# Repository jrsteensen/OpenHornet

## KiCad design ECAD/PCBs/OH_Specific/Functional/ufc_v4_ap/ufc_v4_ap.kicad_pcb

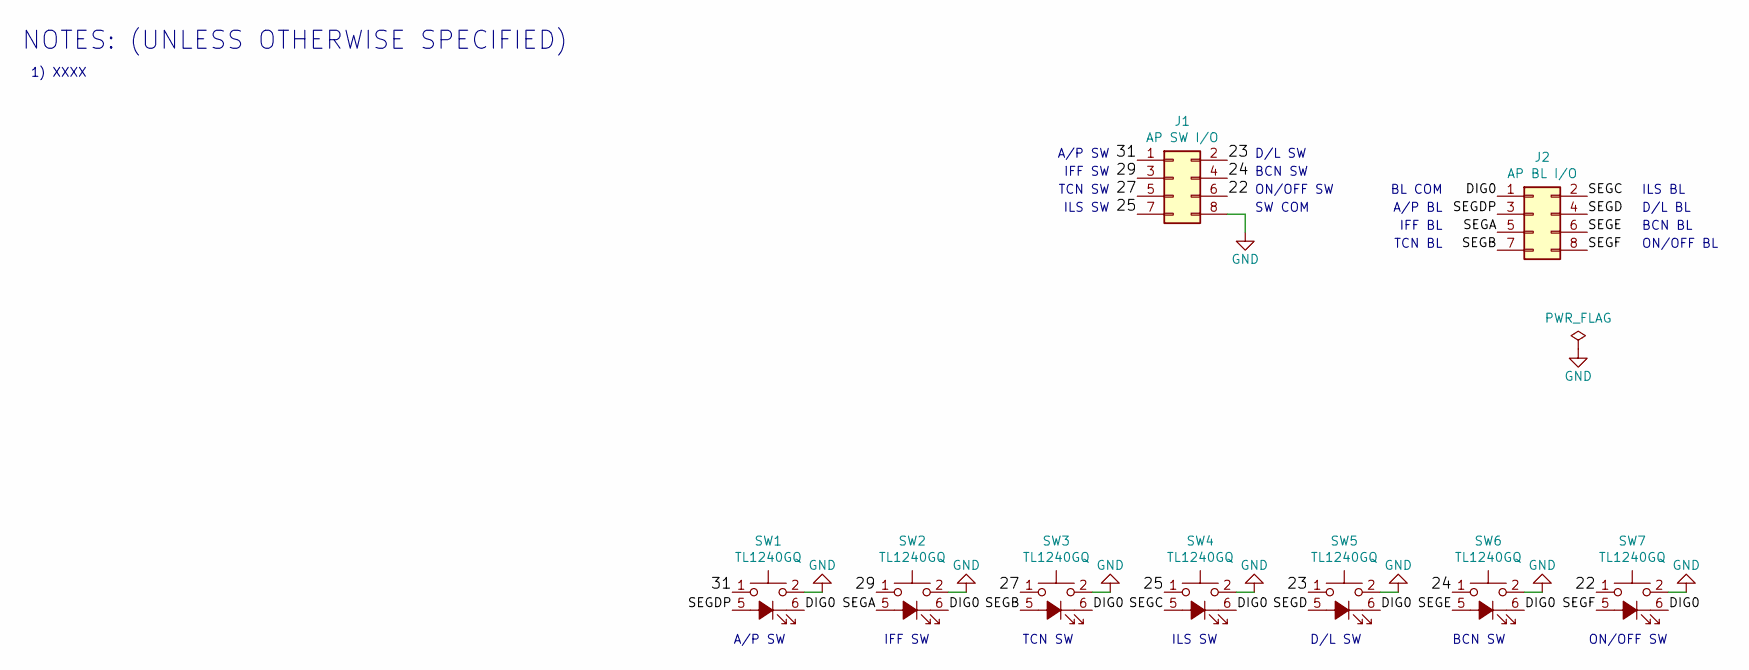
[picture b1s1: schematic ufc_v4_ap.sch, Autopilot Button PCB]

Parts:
J1: AP SW I/O; PinHeader_2x04_P2.54mm_Vertical
J2: AP BL I/O; PinHeader_2x04_P2.54mm_Vertical
SW1, SW2, SW3, SW4, SW5, SW6, SW7: TL1240GQ

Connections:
/22: J1.6, SW7.1
/23: J1.2, SW5.1
/24: J1.4, SW6.1
/25: J1.7, SW4.1
/27: J1.5, SW3.1
/29: J1.3, SW2.1
/31: J1.1, SW1.1
/DIG0: J2.1, SW1.6, SW2.6, SW3.6, SW4.6, SW5.6, SW6.6, SW7.6
/SEGA: J2.5, SW2.5 (K)
/SEGB: J2.7, SW3.5 (K)
/SEGC: J2.2, SW4.5 (K)
/SEGD: J2.4, SW5.5 (K)
/SEGDP: J2.3, SW1.5 (K)
/SEGE: J2.6, SW6.5 (K)
/SEGF: J2.8, SW7.5 (K)
GND: J1.8, SW1.2, SW2.2, SW3.2, SW4.2, SW5.2, SW6.2, SW7.2

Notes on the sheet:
NOTES: (UNLESS OTHERWISE SPECIFIED)
1) XXXX
A/P SW
IFF SW
TCN SW
ILS SW
D/L SW
BCN SW
ON/OFF SW
BL COM
A/P BL
IFF BL
TCN BL
ILS BL
D/L BL
BCN BL
ON/OFF BL
SW COM

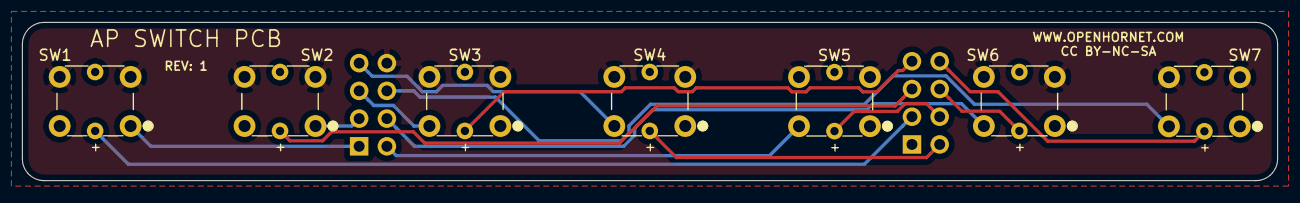
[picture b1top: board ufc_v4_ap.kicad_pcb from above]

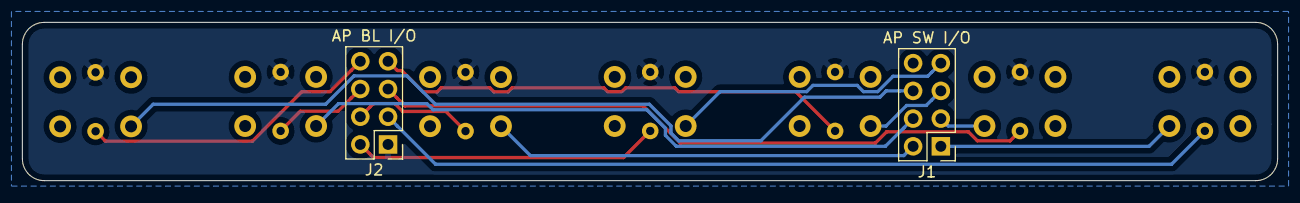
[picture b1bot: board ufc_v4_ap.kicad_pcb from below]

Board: 2 copper layers, 115.0 x 14.5 mm, 9 parts (2 on the bottom side), 16 nets.

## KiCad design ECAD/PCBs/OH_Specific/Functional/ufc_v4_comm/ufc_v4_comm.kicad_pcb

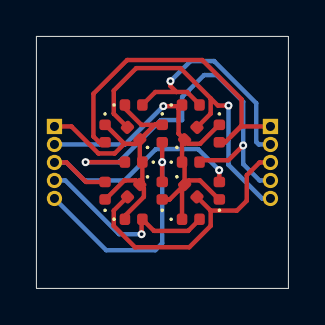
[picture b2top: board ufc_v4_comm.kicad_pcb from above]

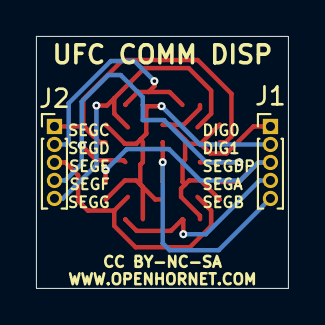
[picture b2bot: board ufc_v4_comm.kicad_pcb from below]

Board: 2 copper layers, 14.0 x 14.0 mm, 18 parts (2 on the bottom side), 10 nets.

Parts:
D1, D2, D3, D4, D5, D6, D7, D8, D9, D10, D11, D12, D13, D14, D15, D16: LED; LED_0402_1005Metric
J1, J2: Conn_01x05_Male; PinHeader_1x05_P1.00mm_Vertical

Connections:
/DIG0: D1.1, D2.1, D3.1, D4.1, D5.1, D6.1, D7.1, D8.1, J1.1
/DIG1: D9.1, D10.1, D11.1, D12.1, D13.1, D14.1, D15.1, D16.1, J1.2
/SEGA: D7.2, D14.2, J1.4
/SEGB: D8.2, D9.2, J1.5
/SEGC: D1.2, D15.2, J2.1
/SEGD: D3.2, D10.2, J2.2
/SEGDP: D2.2, D16.2, J1.3
/SEGE: D6.2, D13.2, J2.3
/SEGF: D5.2, D12.2, J2.4
/SEGG: D4.2, D11.2, J2.5

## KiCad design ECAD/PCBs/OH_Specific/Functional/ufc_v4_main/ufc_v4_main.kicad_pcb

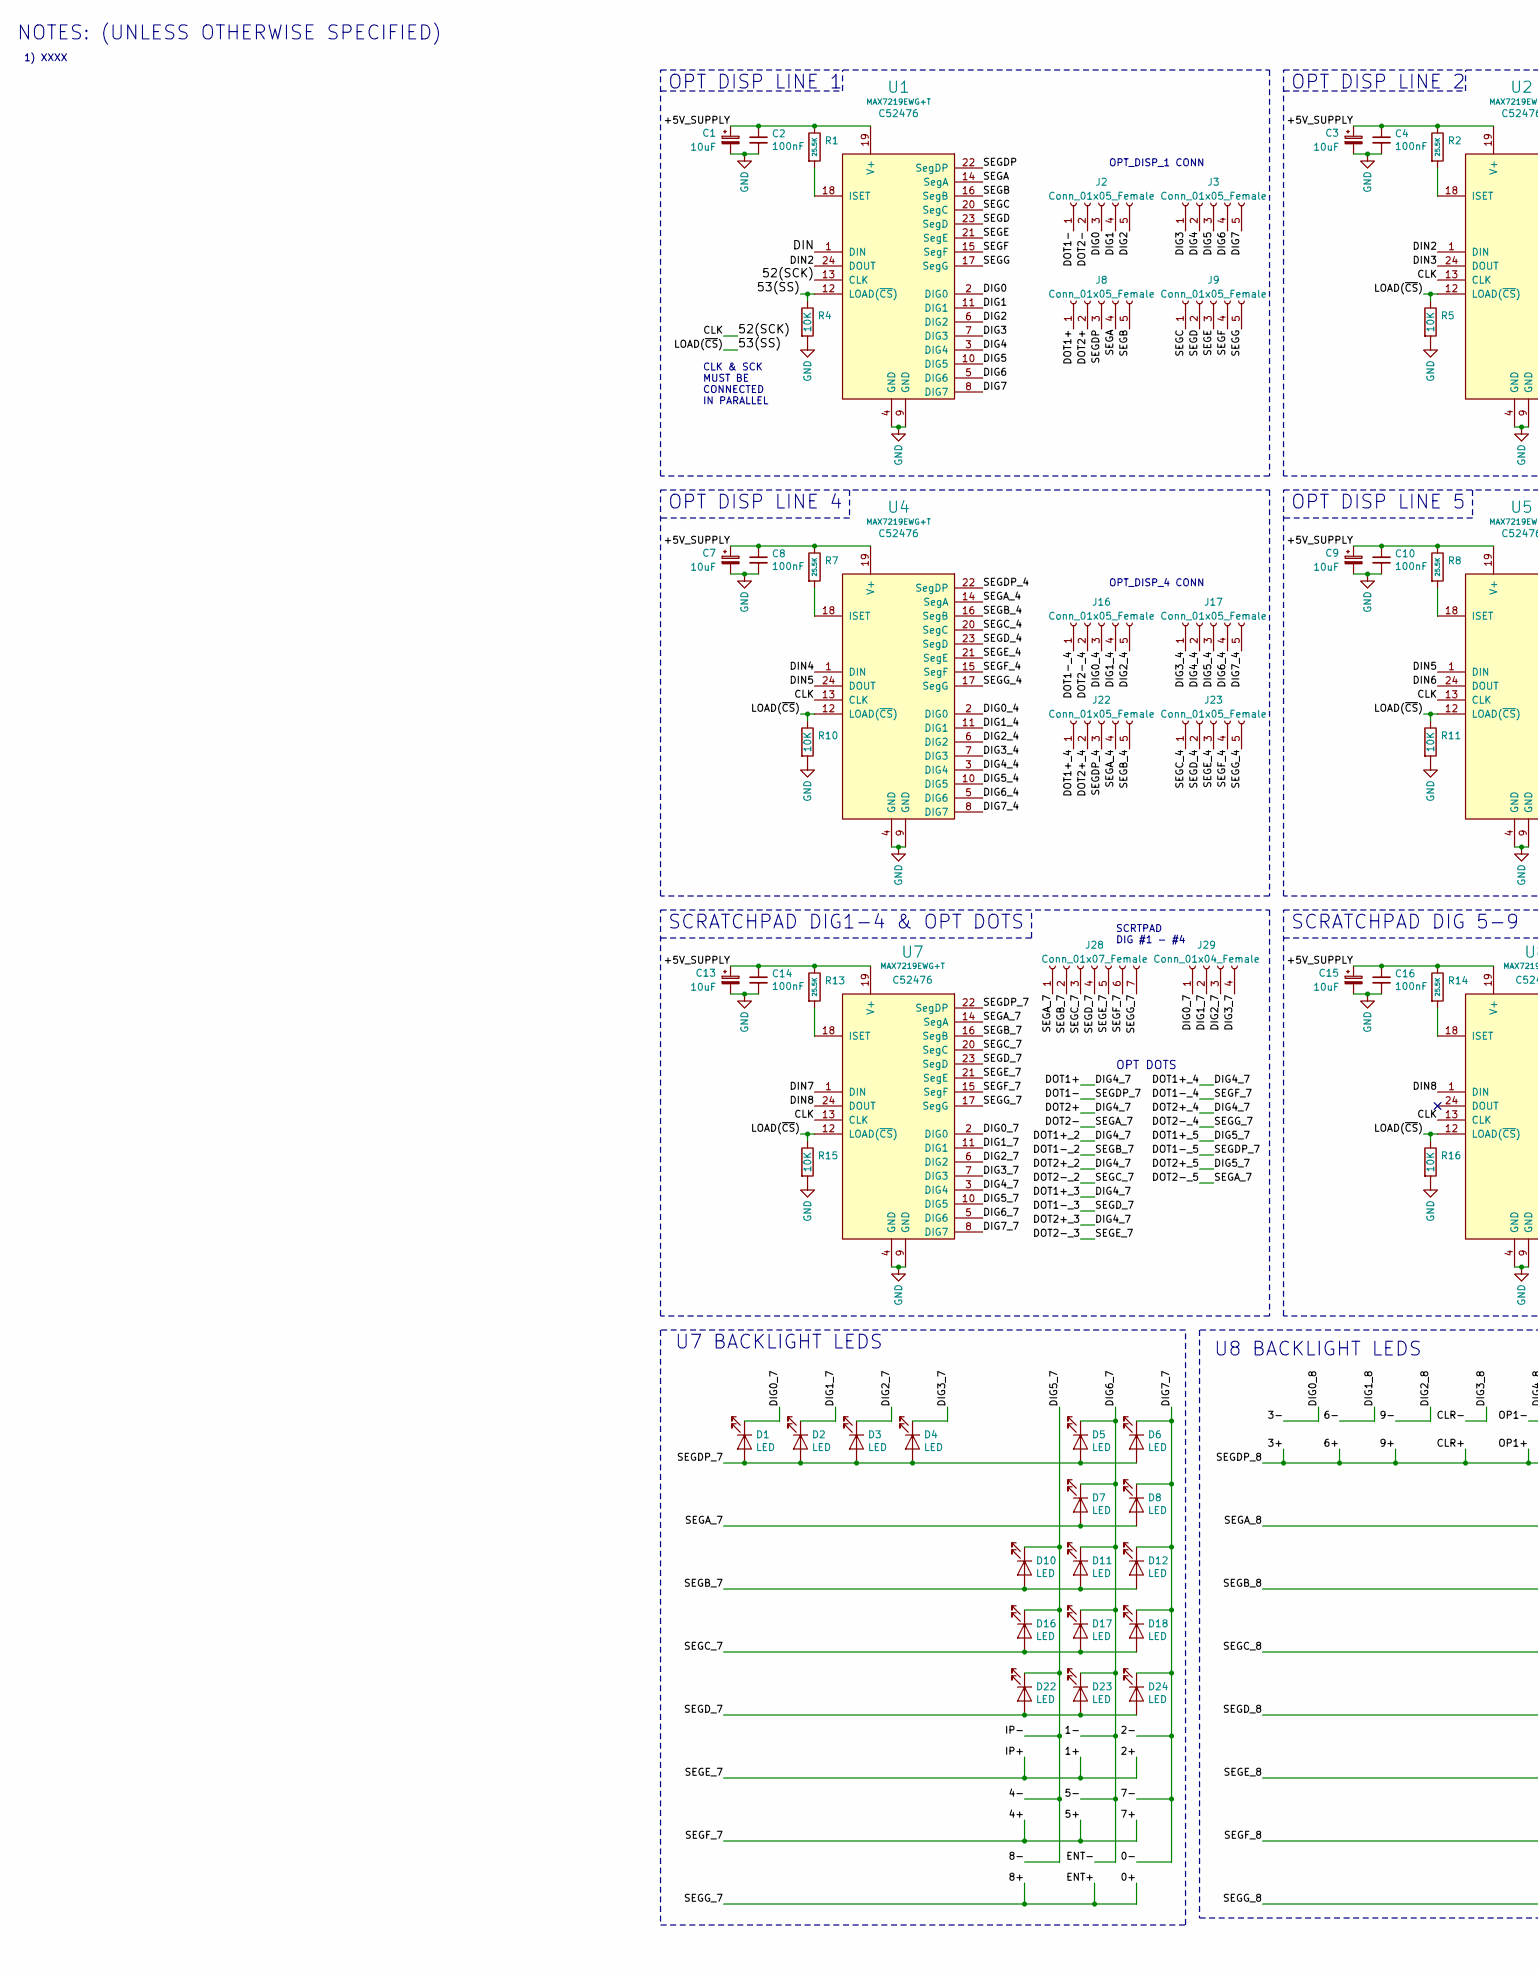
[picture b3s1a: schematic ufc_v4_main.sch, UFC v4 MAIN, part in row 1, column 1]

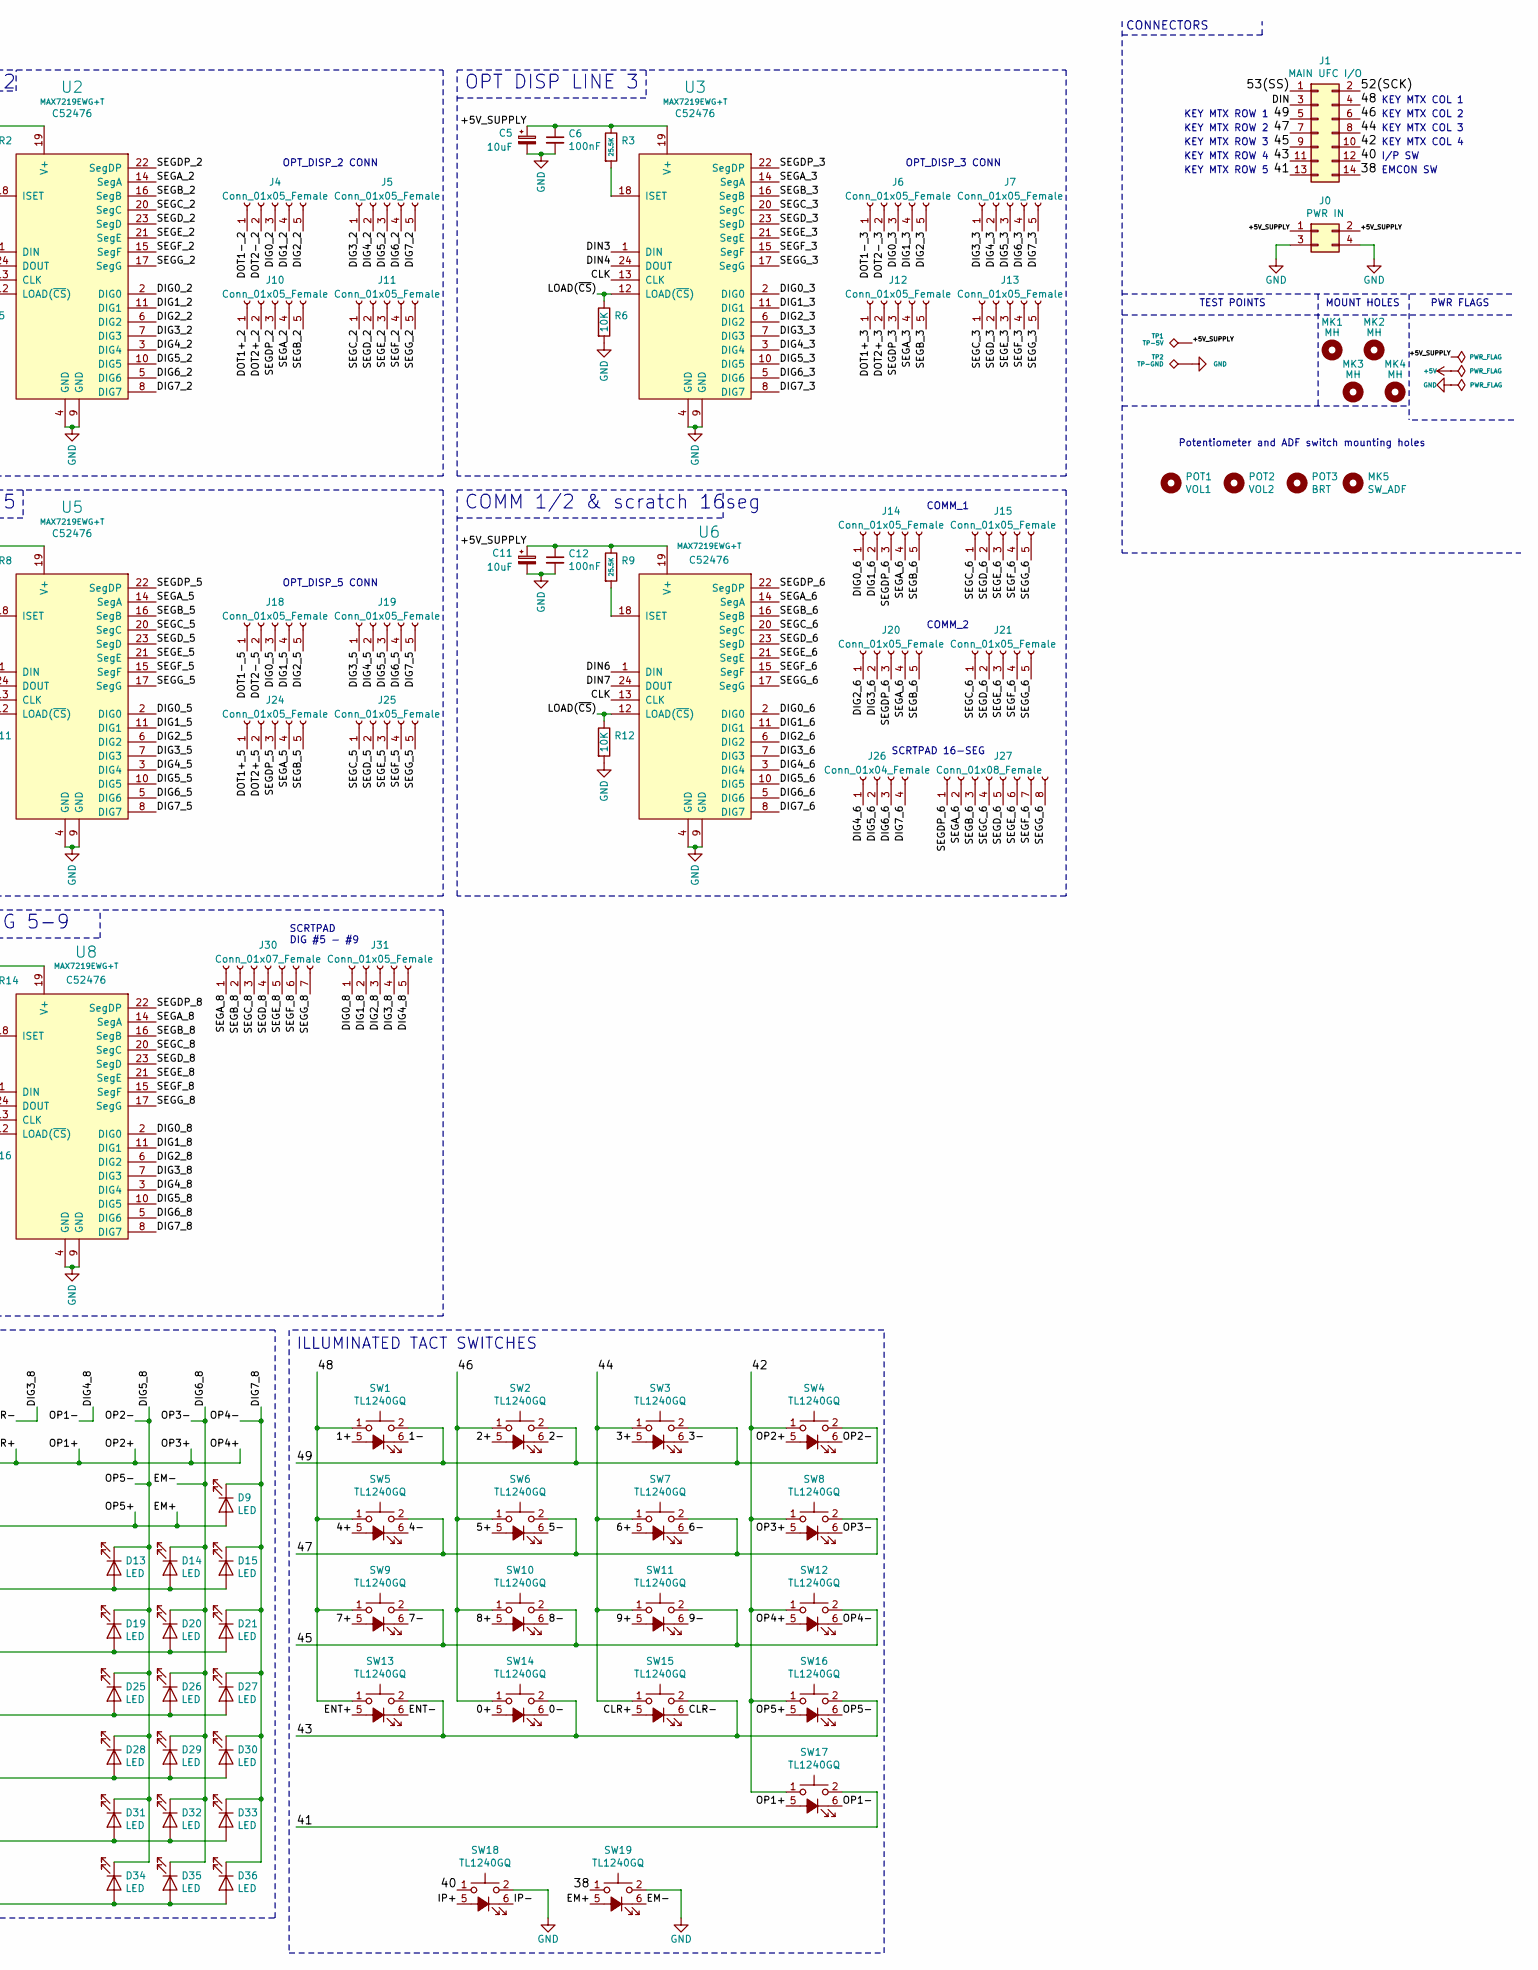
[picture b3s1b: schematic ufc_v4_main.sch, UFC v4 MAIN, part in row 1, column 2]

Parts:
C1, C3, C5, C7, C9, C11, C13, C15: 10uF; CP_Elec_4x5.3; LCSC C134721
C2, C4, C6, C8, C10, C12, C14, C16: 100nF; C_0402_1005Metric; LCSC C1525
D1, D2, D3, D4, D5, D6, D7, D8, D9, D10, D11, D12, D13, D14, D15, D16, D17, D18, D19, D20, D21, D22, D23, D24, D25, D26, D27, D28, D29, D30, D31, D32, D33, D34, D35, D36: LED; LED_0402_1005Metric; LCSC C130723
J0: PWR IN; Molex_Mini-Fit_Jr_5566-04A_2x02_P4.20mm_Vertical
J1: MAIN UFC I/O; PinHeader_2x07_P2.54mm_Vertical
J2, J3, J4, J5, J6, J7, J8, J9, J10, J11, J12, J13, J14, J15, J16, J17, J18, J19, J20, J21, J22, J23, J24, J25, J31: Conn_01x05_Female; PinSocket_1x05_P1.00mm_Vertical
J26, J29: Conn_01x04_Female; PinSocket_1x04_P1.00mm_Vertical
J27: Conn_01x08_Female; PinSocket_1x08_P1.00mm_Vertical
J28, J30: Conn_01x07_Female; PinSocket_1x07_P1.00mm_Vertical
MK1, MK2, MK3, MK4: MH; MountingHole_4.3mm_M4
MK5: SW_ADF; MountingHole_6.4mm_M6
POT1: VOL1; BR10K_Pot_11mm_x_11mm
POT2: VOL2; BR10K_Pot_11mm_x_11mm
POT3: BRT; BR10K_Pot_11mm_x_11mm
R1, R2, R3, R7, R8, R9, R13, R14: 25.5K; R_0603_1608Metric; LCSC C22920
R4, R5, R6, R10, R11, R12, R15, R16: 10K; R_0603_1608Metric; LCSC C25804
SW1, SW2, SW3, SW4, SW5, SW6, SW7, SW8, SW9, SW10, SW11, SW12, SW13, SW14, SW15, SW16, SW17, SW18, SW19: TL1240GQ
TP1: TP-5V; TestPoint_THTPad_D1.5mm_Drill0.7mm
TP2: TP-GND; TestPoint_THTPad_D1.5mm_Drill0.7mm
U1, U2, U3, U4, U5, U6, U7, U8: MAX7219EWG+T; SOIC-24W_7.5x15.4mm_P1.27mm; LCSC C52476

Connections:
/0+: J16.2, J28.7, SW10.5 (K), SW13.5 (K), SW14.5 (K), U7.17 (SegG)
/0-: D6.1 (K), D8.1 (K), D12.1 (K), D18.1 (K), D24.1 (K), SW2.6, SW9.6, SW14.6, U7.8 (DIG7)
/1+: J6.2, J28.5, SW1.5 (K), SW2.5 (K), SW18.5 (K), U7.21 (SegE)
/1-: D5.1 (K), D7.1 (K), D11.1 (K), D17.1 (K), D23.1 (K), SW1.6, SW6.6, SW13.6, U7.5 (DIG6)
/3+: SW3.5 (K), SW4.5 (K), SW7.5 (K), SW8.5 (K), SW11.5 (K), SW12.5 (K), SW15.5 (K), SW17.5 (K), U8.22 (SegDP)
/3-: J31.1, SW3.6, U8.2 (DIG0)
/4+: J16.1, J28.6, SW5.5 (K), SW6.5 (K), SW9.5 (K), U7.15 (SegF)
/4-: D10.1 (K), D16.1 (K), D22.1 (K), J24.1, J24.2, SW5.6, SW10.6, SW18.6, U7.10 (DIG5)
/6-: J31.2, SW7.6, U8.11 (DIG1)
/9-: J31.3, SW11.6, U8.6 (DIG2)
/38: J1.14, SW19.1
/40: J1.12, SW18.1
/41: J1.13, SW17.2
/42: J1.10, SW4.1, SW8.1, SW12.1, SW16.1, SW17.1
/43: J1.11, SW13.2, SW14.2, SW15.2, SW16.2
/44: J1.8, SW3.1, SW7.1, SW11.1, SW15.1
/45: J1.9, SW9.2, SW10.2, SW11.2, SW12.2
/46: J1.6, SW2.1, SW6.1, SW10.1, SW14.1
/47: J1.7, SW5.2, SW6.2, SW7.2, SW8.2
/48: J1.4, SW1.1, SW5.1, SW9.1, SW13.1
/49: J1.5, SW1.2, SW2.2, SW3.2, SW4.2
/52(SCK): J1.2, U1.13 (CLK), U2.13 (CLK), U3.13 (CLK), U4.13 (CLK), U5.13 (CLK), U6.13 (CLK), U7.13 (CLK), U8.13 (CLK)
/53(SS): J1.1, R4.1, R5.1, R6.1, R10.1, R11.1, R12.1, R15.1, R16.1, U1.12 (LOAD(~CS)), U2.12 (LOAD(~CS)), U3.12 (LOAD(~CS)), U4.12 (LOAD(~CS)), U5.12 (LOAD(~CS)), U6.12 (LOAD(~CS)), U7.12 (LOAD(~CS)), U8.12 (LOAD(~CS))
/+5V_SUPPLY: C1.1, C2.1, C3.1, C4.1, C5.1, C6.1, C7.1, C8.1, C9.1, C10.1, C11.1, C12.1, C13.1, C14.1, C15.1, C16.1, J0.1, J0.2, R1.1, R2.1, R3.1, R7.1, R8.1, R9.1, R13.1, R14.1, TP1.1, U1.19 (V+), U2.19 (V+), U3.19 (V+), U4.19 (V+), U5.19 (V+), U6.19 (V+), U7.19 (V+), U8.19 (V+)
/CLR-: J31.4, SW15.6, U8.7 (DIG3)
/DIG0: J2.3, U1.2 (DIG0)
/DIG0_2: J4.3, U2.2 (DIG0)
/DIG0_3: J6.3, U3.2 (DIG0)
/DIG0_4: J16.3, U4.2 (DIG0)
/DIG0_5: J18.3, U5.2 (DIG0)
/DIG0_6: J14.1, U6.2 (DIG0)
/DIG0_7: D1.1 (K), J29.1, U7.2 (DIG0)
/DIG1: J2.4, U1.11 (DIG1)
/DIG1_2: J4.4, U2.11 (DIG1)
/DIG1_3: J6.4, U3.11 (DIG1)
/DIG1_4: J16.4, U4.11 (DIG1)
/DIG1_5: J18.4, U5.11 (DIG1)
/DIG1_6: J14.2, U6.11 (DIG1)
/DIG1_7: D2.1 (K), J29.2, U7.11 (DIG1)
/DIG2: J2.5, U1.6 (DIG2)
/DIG2_2: J4.5, U2.6 (DIG2)
/DIG2_3: J6.5, U3.6 (DIG2)
/DIG2_4: J16.5, U4.6 (DIG2)
/DIG2_5: J18.5, U5.6 (DIG2)
/DIG2_6: J20.1, U6.6 (DIG2)
/DIG2_7: D3.1 (K), J29.3, U7.6 (DIG2)
/DIG3: J3.1, U1.7 (DIG3)
/DIG3_2: J5.1, U2.7 (DIG3)
/DIG3_3: J7.1, U3.7 (DIG3)
/DIG3_4: J17.1, U4.7 (DIG3)
/DIG3_5: J19.1, U5.7 (DIG3)
/DIG3_6: J20.2, U6.7 (DIG3)
/DIG3_7: D4.1 (K), J29.4, U7.7 (DIG3)
/DIG4: J3.2, U1.3 (DIG4)
/DIG4_2: J5.2, U2.3 (DIG4)
/DIG4_3: J7.2, U3.3 (DIG4)
/DIG4_4: J17.2, U4.3 (DIG4)
/DIG4_5: J19.2, U5.3 (DIG4)
/DIG4_6: J26.1, U6.3 (DIG4)
/DIG4_7: J8.1, J8.2, J10.1, J10.2, J12.1, J12.2, J22.1, J22.2, U7.3 (DIG4)
/DIG4_8: J31.5, SW17.6, U8.3 (DIG4)
/DIG5: J3.3, U1.10 (DIG5)
/DIG5_2: J5.3, U2.10 (DIG5)
/DIG5_3: J7.3, U3.10 (DIG5)
/DIG5_4: J17.3, U4.10 (DIG5)
/DIG5_5: J19.3, U5.10 (DIG5)
/DIG5_6: J26.2, U6.10 (DIG5)
/DIG5_8: D13.1 (K), D19.1 (K), D25.1 (K), D28.1 (K), D31.1 (K), D34.1 (K), SW4.6, SW16.6, U8.10 (DIG5)
/DIG6: J3.4, U1.5 (DIG6)
/DIG6_2: J5.4, U2.5 (DIG6)
/DIG6_3: J7.4, U3.5 (DIG6)
/DIG6_4: J17.4, U4.5 (DIG6)
/DIG6_5: J19.4, U5.5 (DIG6)
/DIG6_6: J26.3, U6.5 (DIG6)
/DIG6_8: D14.1 (K), D20.1 (K), D26.1 (K), D29.1 (K), D32.1 (K), D35.1 (K), SW8.6, SW19.6, U8.5 (DIG6)
/DIG7: J3.5, U1.8 (DIG7)
/DIG7_2: J5.5, U2.8 (DIG7)
/DIG7_3: J7.5, U3.8 (DIG7)
/DIG7_4: J17.5, U4.8 (DIG7)
/DIG7_5: J19.5, U5.8 (DIG7)
/DIG7_6: J26.4, U6.8 (DIG7)
/DIG7_8: D9.1 (K), D15.1 (K), D21.1 (K), D27.1 (K), D30.1 (K), D33.1 (K), D36.1 (K), SW12.6, U8.8 (DIG7)
/DIN: J1.3, U1.1 (DIN)
/DIN2: U1.24 (DOUT), U2.1 (DIN)
/DIN3: U2.24 (DOUT), U3.1 (DIN)
/DIN4: U3.24 (DOUT), U4.1 (DIN)
/DIN5: U4.24 (DOUT), U5.1 (DIN)
/DIN6: U5.24 (DOUT), U6.1 (DIN)
/DIN7: U6.24 (DOUT), U7.1 (DIN)
/DIN8: U7.24 (DOUT), U8.1 (DIN)
/DOT1-: D1.2 (A), D2.2 (A), D3.2 (A), D4.2 (A), D5.2 (A), D6.2 (A), J2.1, J18.1, U7.22 (SegDP)
/DOT1-_2: D10.2 (A), D11.2 (A), D12.2 (A), J4.1, J28.2, U7.16 (SegB)
/DOT1-_3: D22.2 (A), D23.2 (A), D24.2 (A), J6.1, J28.4, U7.23 (SegD)
/DOT2-: D7.2 (A), D8.2 (A), J2.2, J18.2, J28.1, U7.14 (SegA)
/DOT2-_2: D16.2 (A), D17.2 (A), D18.2 (A), J4.2, J28.3, U7.20 (SegC)
/EM+: D9.2 (A), J30.1, SW16.5 (K), SW19.5 (K), U8.14 (SegA)
/SEGA: J8.4, U1.14 (SegA)
/SEGA_2: J10.4, U2.14 (SegA)
/SEGA_3: J12.4, U3.14 (SegA)
/SEGA_4: J22.4, U4.14 (SegA)
/SEGA_5: J24.4, U5.14 (SegA)
/SEGA_6: J14.4, J20.4, J27.2, U6.14 (SegA)
/SEGB: J8.5, U1.16 (SegB)
/SEGB_2: J10.5, U2.16 (SegB)
/SEGB_3: J12.5, U3.16 (SegB)
/SEGB_4: J22.5, U4.16 (SegB)
/SEGB_5: J24.5, U5.16 (SegB)
/SEGB_6: J14.5, J20.5, J27.3, U6.16 (SegB)
/SEGB_8: D13.2 (A), D14.2 (A), D15.2 (A), J30.2, U8.16 (SegB)
/SEGC: J9.1, U1.20 (SegC)
/SEGC_2: J11.1, U2.20 (SegC)
/SEGC_3: J13.1, U3.20 (SegC)
/SEGC_4: J23.1, U4.20 (SegC)
/SEGC_5: J25.1, U5.20 (SegC)
/SEGC_6: J15.1, J21.1, J27.4, U6.20 (SegC)
/SEGC_8: D19.2 (A), D20.2 (A), D21.2 (A), J30.3, U8.20 (SegC)
/SEGD: J9.2, U1.23 (SegD)
/SEGDP: J8.3, U1.22 (SegDP)
/SEGDP_2: J10.3, U2.22 (SegDP)
/SEGDP_3: J12.3, U3.22 (SegDP)
/SEGDP_4: J22.3, U4.22 (SegDP)
/SEGDP_5: J24.3, U5.22 (SegDP)
/SEGDP_6: J14.3, J20.3, J27.1, U6.22 (SegDP)
/SEGD_2: J11.2, U2.23 (SegD)
/SEGD_3: J13.2, U3.23 (SegD)
/SEGD_4: J23.2, U4.23 (SegD)
/SEGD_5: J25.2, U5.23 (SegD)
/SEGD_6: J15.2, J21.2, J27.5, U6.23 (SegD)
/SEGD_8: D25.2 (A), D26.2 (A), D27.2 (A), J30.4, U8.23 (SegD)
/SEGE: J9.3, U1.21 (SegE)
/SEGE_2: J11.3, U2.21 (SegE)
/SEGE_3: J13.3, U3.21 (SegE)
/SEGE_4: J23.3, U4.21 (SegE)
/SEGE_5: J25.3, U5.21 (SegE)
/SEGE_6: J15.3, J21.3, J27.6, U6.21 (SegE)
/SEGE_8: D28.2 (A), D29.2 (A), D30.2 (A), J30.5, U8.21 (SegE)
/SEGF: J9.4, U1.15 (SegF)
/SEGF_2: J11.4, U2.15 (SegF)
/SEGF_3: J13.4, U3.15 (SegF)
/SEGF_4: J23.4, U4.15 (SegF)
/SEGF_5: J25.4, U5.15 (SegF)
/SEGF_6: J15.4, J21.4, J27.7, U6.15 (SegF)
/SEGF_8: D31.2 (A), D32.2 (A), D33.2 (A), J30.6, U8.15 (SegF)
/SEGG: J9.5, U1.17 (SegG)
/SEGG_2: J11.5, U2.17 (SegG)
/SEGG_3: J13.5, U3.17 (SegG)
/SEGG_4: J23.5, U4.17 (SegG)
/SEGG_5: J25.5, U5.17 (SegG)
/SEGG_6: J15.5, J21.5, J27.8, U6.17 (SegG)
/SEGG_8: D34.2 (A), D35.2 (A), D36.2 (A), J30.7, U8.17 (SegG)
GND: C1.2, C2.2, C3.2, C4.2, C5.2, C6.2, C7.2, C8.2, C9.2, C10.2, C11.2, C12.2, C13.2, C14.2, C15.2, C16.2, J0.3, J0.4, R4.2, R5.2, R6.2, R10.2, R11.2, R12.2, R15.2, R16.2, SW18.2, SW19.2, TP2.1, U1.4 (GND), U1.9 (GND), U2.4 (GND), U2.9 (GND), U3.4 (GND), U3.9 (GND), U4.4 (GND), U4.9 (GND), U5.4 (GND), U5.9 (GND), U6.4 (GND), U6.9 (GND), U7.4 (GND), U7.9 (GND), U8.4 (GND), U8.9 (GND)
unnamed: R1.2, U1.18 (ISET)
unnamed: R2.2, U2.18 (ISET)
unnamed: R3.2, U3.18 (ISET)
unnamed: R7.2, U4.18 (ISET)
unnamed: R8.2, U5.18 (ISET)
unnamed: R9.2, U6.18 (ISET)
unnamed: R13.2, U7.18 (ISET)
unnamed: R14.2, U8.18 (ISET)

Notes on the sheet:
CONNECTORS
MOUNT HOLES
PWR FLAGS
TEST POINTS
SCRTPAD 16-SEG
OPT DISP LINE 1
OPT_DISP_1 CONN
OPT_DISP_2 CONN
OPT DISP LINE 2
OPT DISP LINE 3
OPT_DISP_3 CONN
OPT DISP LINE 4
OPT_DISP_4 CONN
OPT DISP LINE 5
OPT_DISP_5 CONN
COMM 1/2 & scratch 16seg
COMM_1
COMM_2
SCRATCHPAD DIG1-4 & OPT DOTS
SCRTPAD DIG #1 - #4
OPT DOTS
SCRATCHPAD DIG 5-9
SCRTPAD DIG #5 - #9
U7 BACKLIGHT LEDS
U8 BACKLIGHT LEDS
ILLUMINATED TACT SWITCHES
CLK & SCK MUST BE CONNECTED IN PARALLEL
NOTES: (UNLESS OTHERWISE SPECIFIED)
KEY MTX ROW 1
KEY MTX ROW 2
KEY MTX ROW 3
KEY MTX ROW 4
KEY MTX COL 1
KEY MTX COL 2
KEY MTX COL 3
KEY MTX COL 4
EMCON SW
I/P SW
KEY MTX ROW 5
1) XXXX

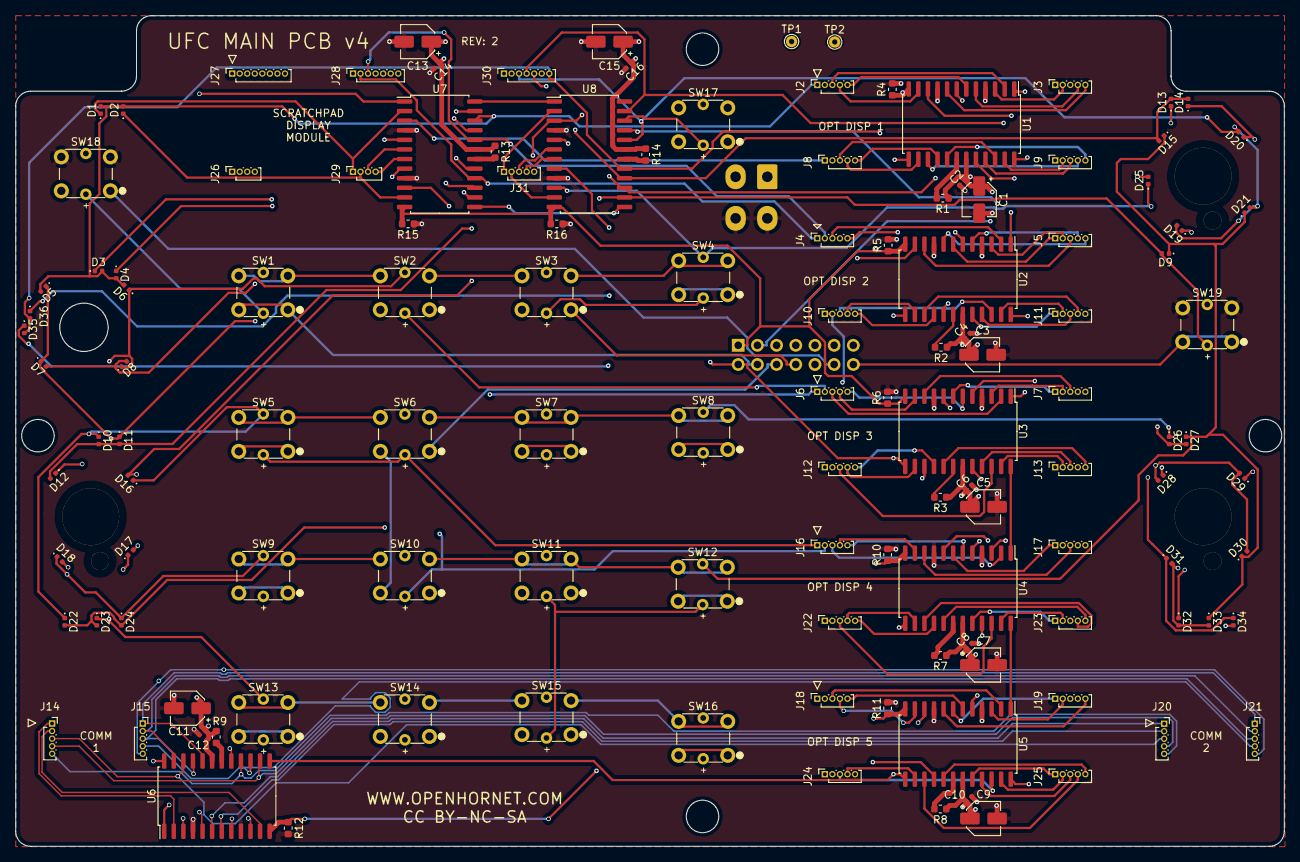
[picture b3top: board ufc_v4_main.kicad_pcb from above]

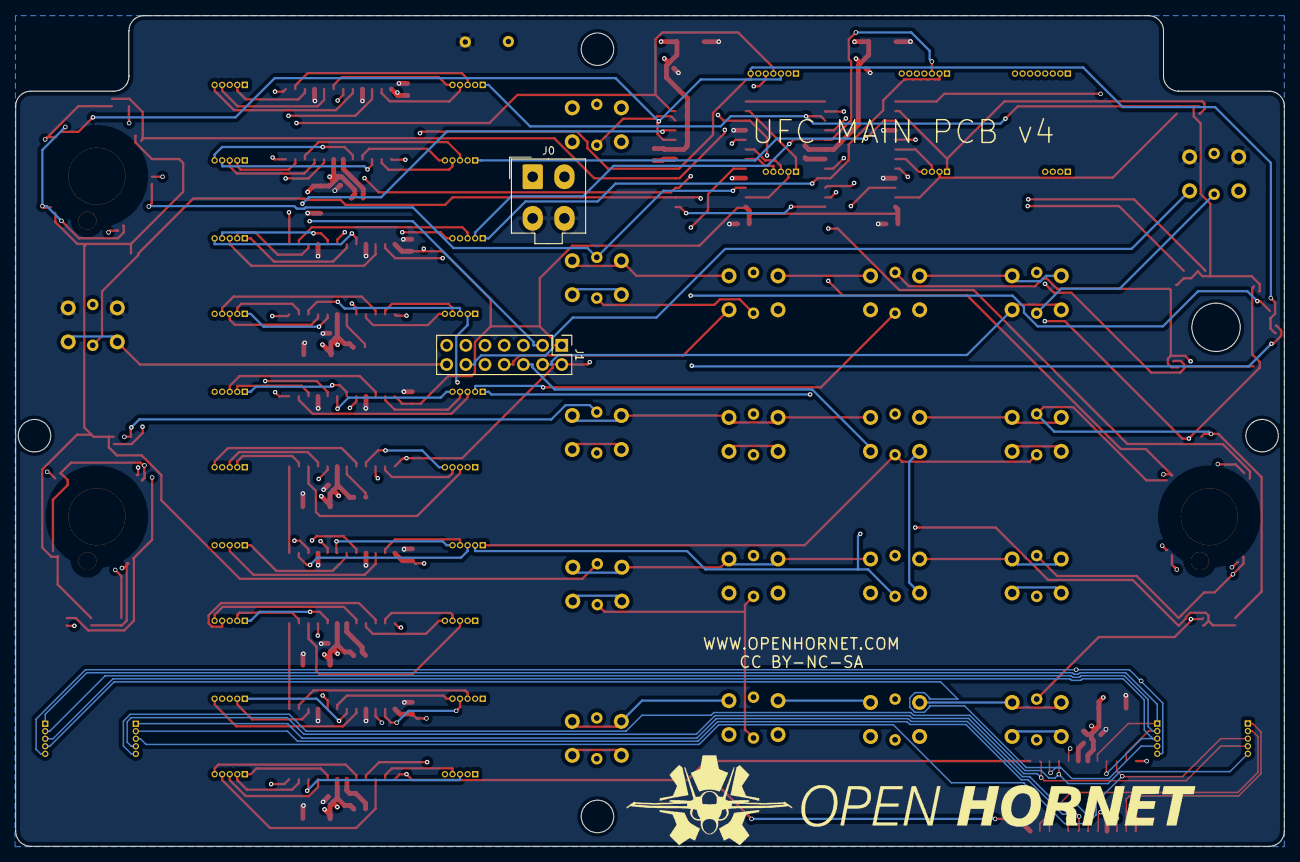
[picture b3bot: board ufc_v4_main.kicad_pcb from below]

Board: 4 copper layers, 168.0 x 110.0 mm, 137 parts (2 on the bottom side), 159 nets.

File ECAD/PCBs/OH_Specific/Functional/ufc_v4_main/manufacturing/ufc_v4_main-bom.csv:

Comment,Designator,Footprint,LCSC Part Number
10uF,"C1,C3,C5,C7,C9,C11,C13,C15",Capacitor_SMD:CP_Elec_4x5.3,C134721
100nF,"C2,C4,C6,C8,C10,C12,C14,C16",Capacitor_SMD:C_0402_1005Metric,C1525
LED,"D1,D2,D3,D4,D5,D6,D7,D8,D9,D10,D11,D12,D13,D14,D15,D16,D17,D18,D19,D20,D21,D22,D23,D24,D25,D26,D27,D28,D29,D30,D31,D32,D33,D34,D35,D36",LED_SMD:LED_0402_1005Metric,C130723
PWR IN,J0,Connector_Molex:Molex_Mini-Fit_Jr_5566-04A_2x02_P4.20mm_Vertical,
MAIN UFC I/O,J1,Connector_PinHeader_2.54mm:PinHeader_2x07_P2.54mm_Vertical,
Conn_01x05_Female,"J2,J3,J4,J5,J6,J7,J8,J9,J10,J11,J12,J13,J14,J15,J16,J17,J18,J19,J20,J21,J22,J23,J24,J25,J31",Connector_PinSocket_1.00mm:PinSocket_1x05_P1.00mm_Vertical,
Conn_01x08_Female,J27,Connector_PinSocket_1.00mm:PinSocket_1x08_P1.00mm_Vertical,
Conn_01x04_Female,"J26,J29",Connector_PinSocket_1.00mm:PinSocket_1x04_P1.00mm_Vertical,
Conn_01x07_Female,"J28,J30",Connector_PinSocket_1.00mm:PinSocket_1x07_P1.00mm_Vertical,
MH,"MK1,MK2,MK3,MK4",MountingHole:MountingHole_4.3mm_M4,
25.5K,"R1,R2,R3,R7,R8,R9,R13,R14",Resistor_SMD:R_0603_1608Metric,C22920
10K,"R4,R5,R6,R10,R11,R12,R15,R16",Resistor_SMD:R_0603_1608Metric,C25804
TL1240GQ,"SW1,SW2,SW3,SW4,SW5,SW6,SW7,SW8,SW9,SW10,SW11,SW12,SW13,SW14,SW15,SW16,SW17,SW18,SW19",KiCAD_Libraries:TL1240GQ,
TP-5V,TP1,TestPoint:TestPoint_THTPad_D1.5mm_Drill0.7mm,
TP-GND,TP2,TestPoint:TestPoint_THTPad_D1.5mm_Drill0.7mm,
MAX7219EWG+T,"U1,U2,U3,U4,U5,U6,U7,U8",Package_SO:SOIC-24W_7.5x15.4mm_P1.27mm,C52476

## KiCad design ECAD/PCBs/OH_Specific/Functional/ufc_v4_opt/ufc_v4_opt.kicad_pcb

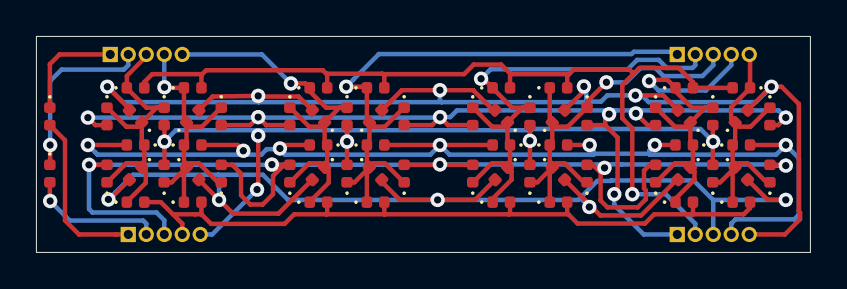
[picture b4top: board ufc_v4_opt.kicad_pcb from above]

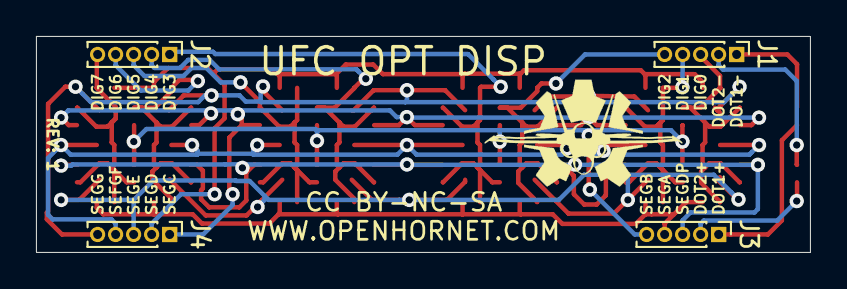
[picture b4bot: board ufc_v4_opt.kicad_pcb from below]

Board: 2 copper layers, 43.0 x 12.0 mm, 70 parts (4 on the bottom side), 20 nets.

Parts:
D1, D2, D3, D4, D5, D6, D7, D8, D9, D10, D11, D12, D13, D14, D15, D16, D17, D18, D19, D20, D21, D22, D23, D24, D25, D26, D27, D28, D29, D30, D31, D32, D33, D34, D35, D36, D37, D38, D39, D40, D41, D42, D43, D44, D45, D46, D47, D48, D49, D50, D51, D52, D53, D54, D55, D56, D57, D58, D59, D60, D61, D62, D63, D64, D65, D66: LED; LED_0402_1005Metric
J1, J2, J3, J4: Conn_01x05_Male; PinHeader_1x05_P1.00mm_Vertical

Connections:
/DIG0: D1.1, D2.1, D3.1, D4.1, D5.1, D6.1, D7.1, D8.1, J1.3
/DIG1: D9.1, D10.1, D11.1, D12.1, D13.1, D14.1, D15.1, D16.1, J1.4
/DIG2: D17.1, D18.1, D19.1, D20.1, D21.1, D22.1, D23.1, D24.1, J1.5
/DIG3: D25.1, D26.1, D27.1, D28.1, D29.1, D30.1, D31.1, D32.1, J2.1
/DIG4: D33.1, D34.1, D35.1, D36.1, D37.1, D38.1, D39.1, D40.1, J2.2
/DIG5: D41.1, D42.1, D43.1, D44.1, D45.1, D46.1, D47.1, D48.1, J2.3
/DIG6: D49.1, D50.1, D51.1, D52.1, D53.1, D54.1, D55.1, D56.1, J2.4
/DIG7: D57.1, D58.1, D59.1, D60.1, D61.1, D62.1, D63.1, D64.1, J2.5
/DOT1+: D65.2, J3.1
/DOT1-: D65.1, J1.1
/DOT2+: D66.2, J3.2
/DOT2-: D66.1, J1.2
/SEGA: D7.2, D14.2, D23.2, D30.2, D39.2, D46.2, D55.2, D62.2, J3.4
/SEGB: D8.2, D9.2, D24.2, D25.2, D40.2, D41.2, D56.2, D57.2, J3.5
/SEGC: D1.2, D15.2, D17.2, D31.2, D33.2, D47.2, D49.2, D63.2, J4.1
/SEGD: D3.2, D10.2, D19.2, D26.2, D35.2, D42.2, D51.2, D58.2, J4.2
/SEGDP: D2.2, D16.2, D18.2, D32.2, D34.2, D48.2, D50.2, D64.2, J3.3
/SEGE: D6.2, D13.2, D22.2, D29.2, D38.2, D45.2, D54.2, D61.2, J4.3
/SEGF: D5.2, D12.2, D21.2, D28.2, D37.2, D44.2, D53.2, D60.2, J4.4
/SEGG: D4.2, D11.2, D20.2, D27.2, D36.2, D43.2, D52.2, D59.2, J4.5

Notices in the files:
ECAD/PCBs/OH_Specific/Functional/ufc_v4_ap/ufc_v4_ap.kicad_pcb:
CC BY-NC-SA
